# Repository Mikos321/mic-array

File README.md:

# Spidermic
 
Spidermic is an low cost circular microphone array. For use in audio measurement applications such as [ambisonics](https://github.com/AppliedAcousticsChalmers/ambisonics-for-insta360-pro).
## Features
* Low cost spherical microphone array with up to 15 omnidirection microphones.
* Plug and play compatible with [Minidsp MCHstreamer](https://www.minidsp.com/products/usb-audio-interface/mchstreamer-lite).
* 15 PDM Infineon M73D122V01 Microphones.
* No programming required!
## Repository Organization
* [kicad/](kicad/) - KiCad schematic, layout and fabrication files for both the main PCB and microhpones
* [mounts/](mounts/) - STL Files for the ring mount.
## Documentation
The main board has 15 flatflex connectors, with a 24 degree angle between them, which allows for the microphones to be mounted equidistant to each other on the hemisphere of an wooden sphere with a radius of 60mm.
### Minidsp MCH-Streamer
The main board of the mic array is mounted on top of a MiniDSP MCH-Streamer connected to J2. 
Since the Infineon microphones work with 1.8v logic and the MCH-steamer only outputs 3.3v, I used Ti-SN74LVC8T245
level shifting from 3.3V to 1.8V of the data and clock signals to and from the MCH-streamer.
### Hand solder
While it should be possible to hand solder the current version of the main board, it might be tricky since components are somewhat tightly placed around the pinheader. This should get fixed in future versions.
I cannot recommend handsoldering the microphone boards since the microphones are very particular with paste application and temperature.
JLCpcba PCBA worked with well for the microphones.
### Mounting hardware
The ring mount should be printed in PETG,fit around the sphere and the microphones are also friction fit in the "claws". 
Squeezing the ring to spread the claws makes it easier to mount the microphones as the tolerances are tight.

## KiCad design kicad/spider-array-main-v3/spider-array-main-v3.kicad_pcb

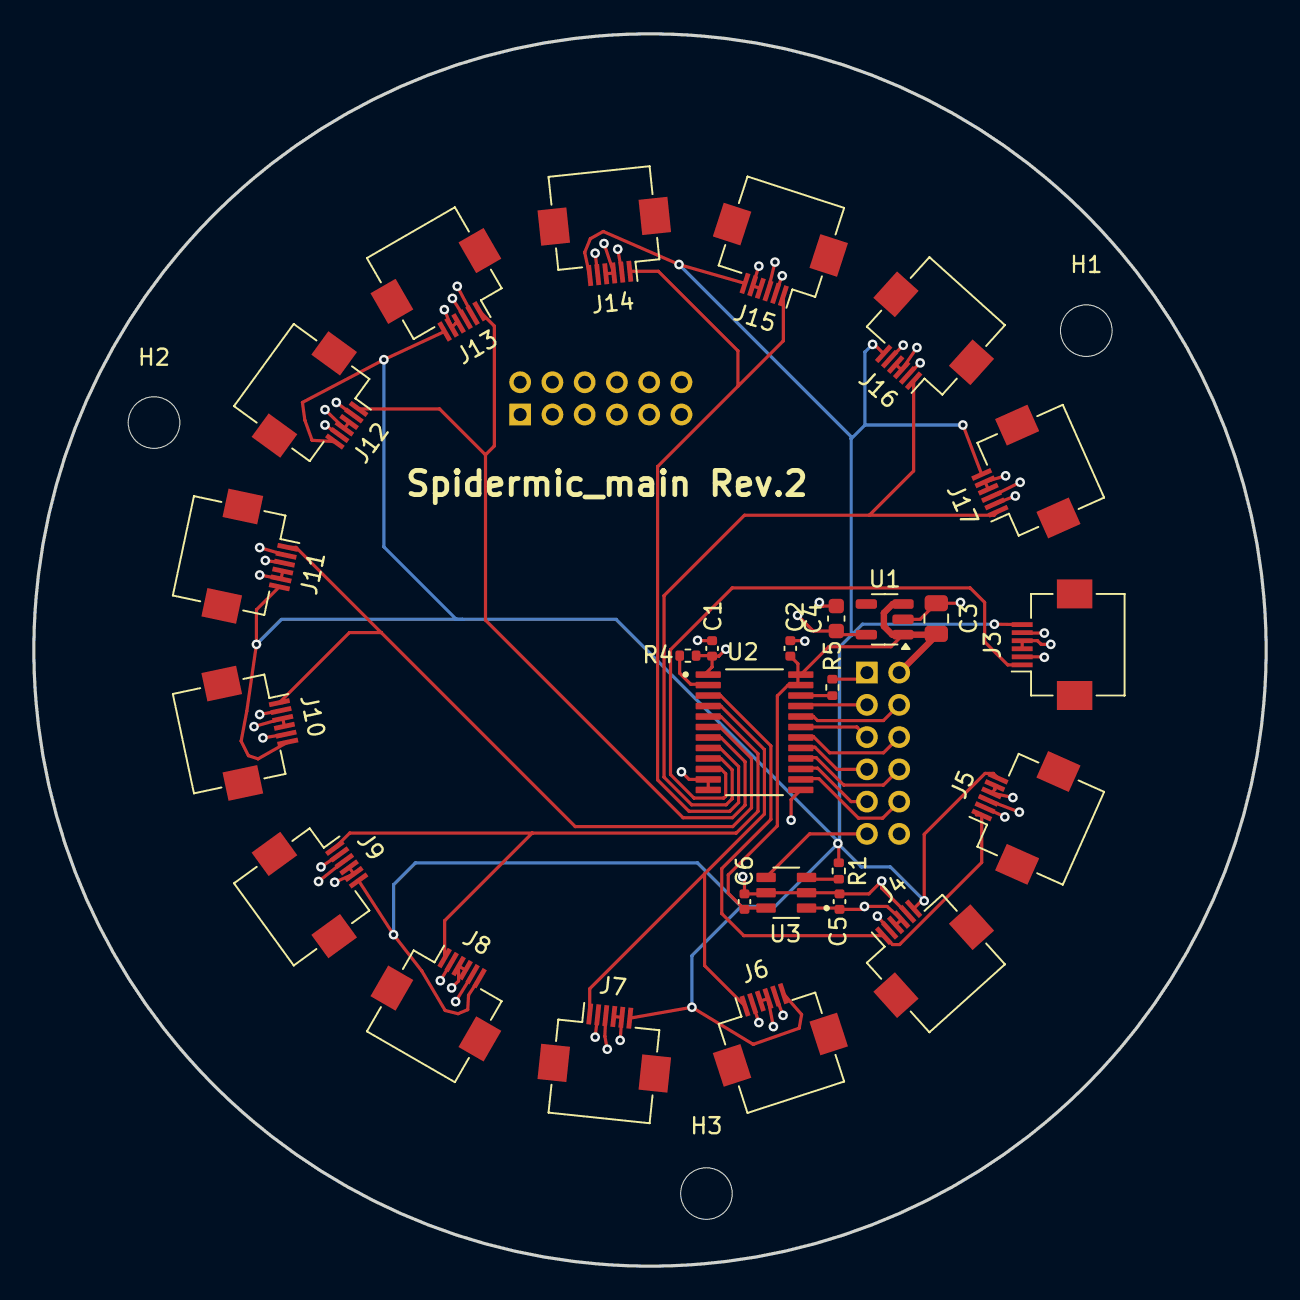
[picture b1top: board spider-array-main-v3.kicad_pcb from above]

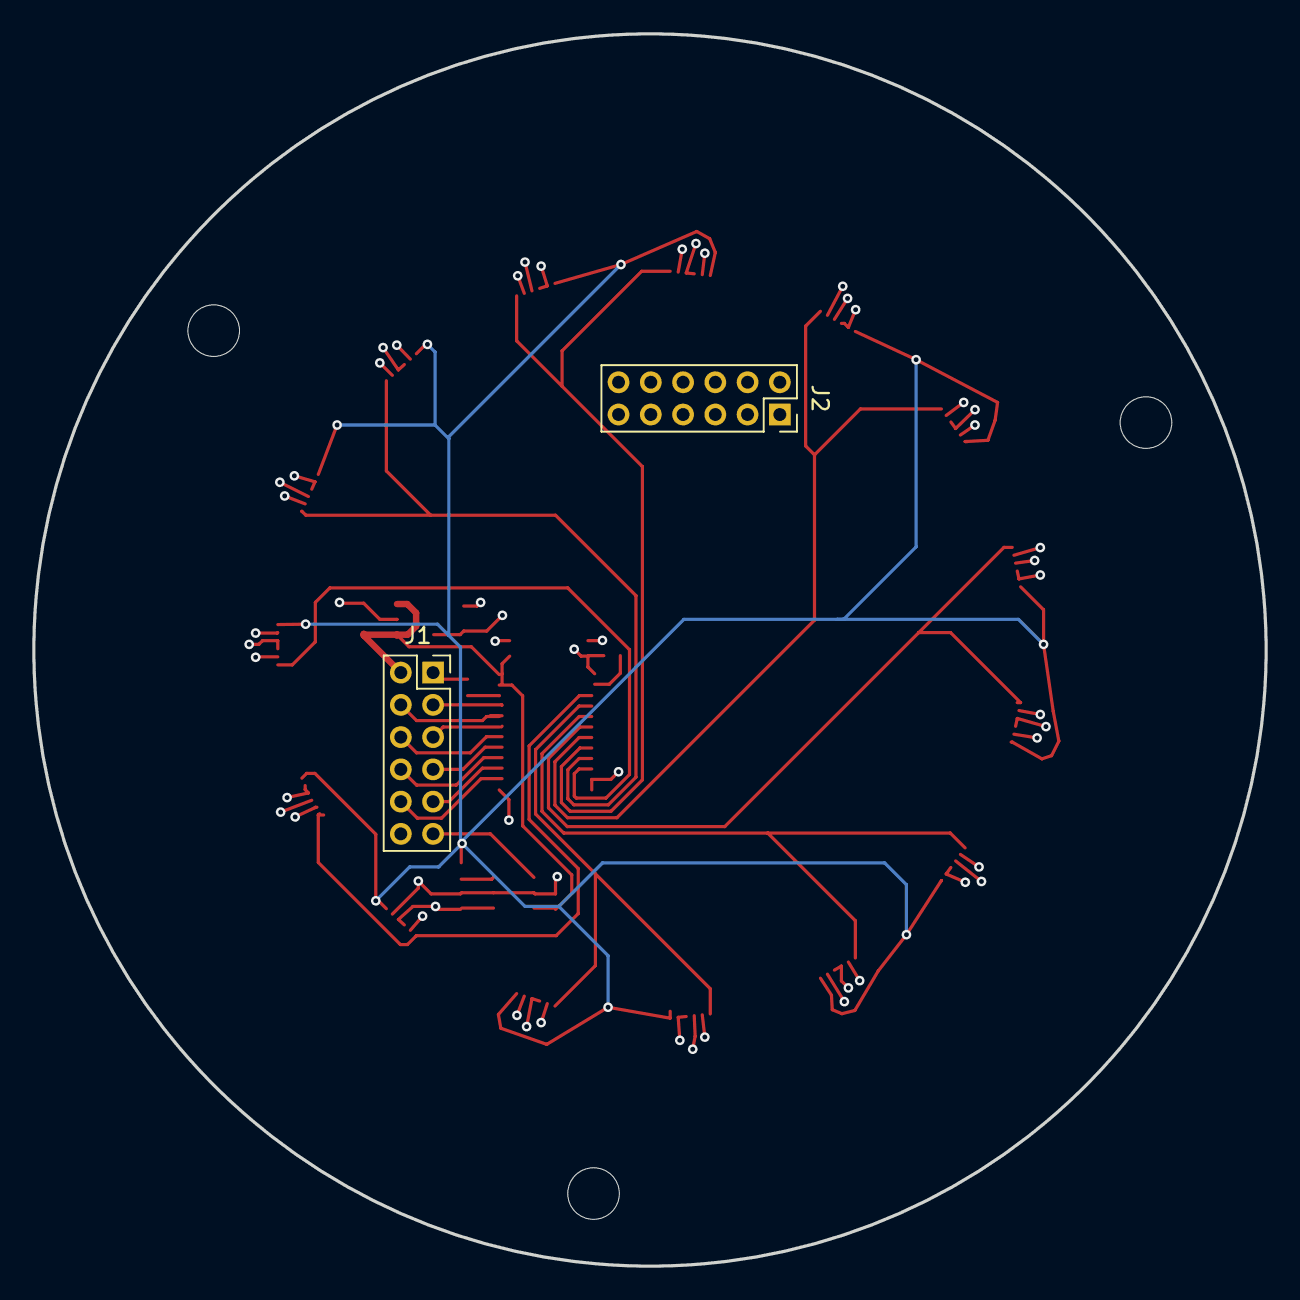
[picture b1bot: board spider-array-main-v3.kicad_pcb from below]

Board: 4 copper layers, 76.4 x 76.4 mm, 32 parts (2 on the bottom side), 24 nets.

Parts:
C1, C2, C5, C6: 1µF; C_0402_1005Metric
C3: 22µF; C_0805_2012Metric
C4: 4.7µF; C_0603_1608Metric
H1, H2, H3: MountingHole; MountingHole_3.2mm_M3
J1, J2: MCH-J3; PinSocket_2x06_P2.00mm_Vertical
J3, J4, J5, J6, J7, J8, J9, J10, J11, J12, J13, J14, J15, J16, J17: Conn_01x06_Socket; Hirose_FH12-6S-0.5SH_1x06-1MP_P0.50mm_Horizontal
R1: 220; R_0402_1005Metric
R4, R5: 2K; R_0402_1005Metric
U1: LP5907MFX-1.8; SOT-23-5
U2: SN74LVC8T245PW; SOP65P640X120-24N
U3: SN74AVCH1T45DBVR; SOT95P280X145-6N

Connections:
GND: C1.2, C2.2, C3.2, C4.2, C5.2, C6.2, J1.1, J3.2, J3.5, J4.2, J4.5, J5.2, J5.4, J5.5, J6.2, J6.5, J7.2, J7.4, J7.5, J8.2, J8.5, J9.2, J9.4, J9.5, J10.2, J10.5, J11.2, J11.4, J11.5, J12.2, J12.5, J13.2, J13.4, J13.5, J14.2, J14.5, J15.2, J15.4, J15.5, J16.2, J16.5, J17.2, J17.4, J17.5, R5.1, U1.2 (GND), U2.11 (GND), U2.12 (GND), U2.13 (GND), U3.2 (GND), U3.5 (DIR)
unnamed: R4.2, U2.2 (DIR)
unnamed: R5.2, U2.22 (~OE)
unnamed: R1.2, U3.3 (A)
PDM_CLK_0IN: J1.11, U3.4 (B)
PDM_CLK_1V8: J3.6, J4.6, J5.6, J6.6, J7.6, J8.6, J9.6, J10.6, J11.6, J12.6, J13.6, J14.6, J15.6, J16.6, J17.6, R1.1
PDM_DATA0: J1.3, U2.21 (B1)
PDM_DATA0_1V8: J4.1, J5.1, U2.3 (A1)
PDM_DATA1: J1.4, U2.20 (B2)
PDM_DATA1_1V8: J6.1, J7.1, U2.4 (A2)
PDM_DATA2: J1.5, U2.19 (B3)
PDM_DATA2_1V8: J8.1, J9.1, U2.5 (A3)
PDM_DATA3: J1.6, U2.18 (B4)
PDM_DATA3_1V8: J10.1, J11.1, U2.6 (A4)
PDM_DATA4: J1.7, U2.17 (B5)
PDM_DATA4_1V8: J12.1, J13.1, U2.7 (A5)
PDM_DATA5: J1.8, U2.16 (B6)
PDM_DATA5_1V8: J14.1, J15.1, U2.8 (A6)
PDM_DATA6: J1.9, U2.15 (B7)
PDM_DATA6_1V8: J16.1, J17.1, U2.9 (A7)
PDM_DATA7: J1.10, U2.14 (B8)
PDM_DATA7_1V8: J3.1, U2.10 (A8)
VCCA: C1.1, C4.1, C5.1, J3.3, J3.4, J4.3, J4.4, J5.3, J6.3, J6.4, J7.3, J8.3, J8.4, J9.3, J10.3, J10.4, J11.3, J12.3, J12.4, J13.3, J14.3, J14.4, J15.3, J16.3, J16.4, J17.3, R4.1, U1.5 (OUT), U2.1 (VCCA), U3.1 (VCCA)
VCCB: C2.1, C3.1, C6.1, J1.2, U1.1 (IN), U1.3 (EN), U2.23 (VCCB), U2.24 (VCCB), U3.6 (VCCB)

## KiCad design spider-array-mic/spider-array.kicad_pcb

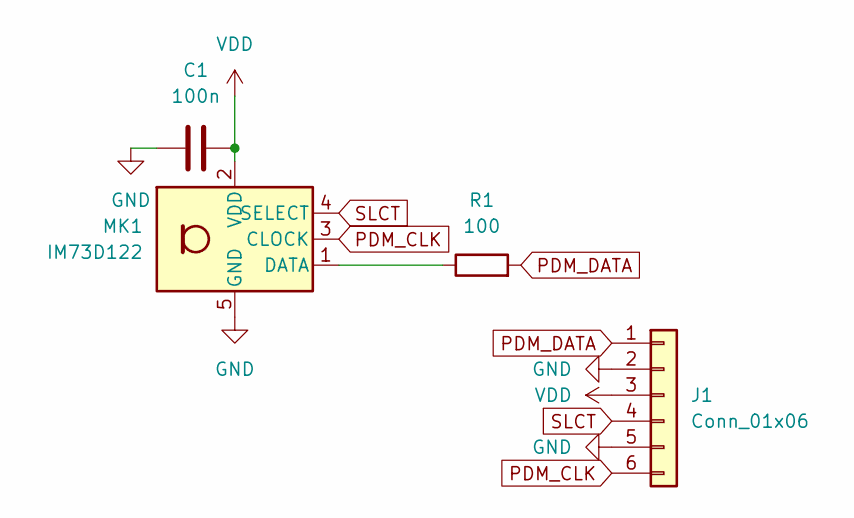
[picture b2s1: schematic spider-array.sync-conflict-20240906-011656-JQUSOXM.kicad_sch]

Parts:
C1: 100n; C_0201_0603Metric
J1: Conn_01x06; Hirose_FH12-6S-0.5SH_1x06-1MP_P0.50mm_Horizontal
MK1: IM73D122; Infineon_PG-LLGA-5-1
R1: 100; R_0201_0603Metric

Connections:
GND: C1.1, J1.2, J1.5, MK1.5 (GND)
unnamed: MK1.1 (DATA), R1.1
PDM_CLK: J1.6, MK1.3 (CLOCK)
PDM_DATA: J1.1, R1.2
SLCT: J1.4, MK1.4 (SELECT)
VDD: C1.2, J1.3, MK1.2 (VDD)

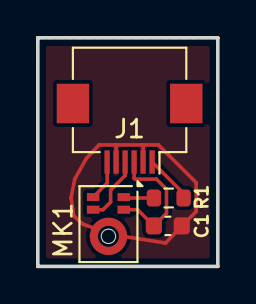
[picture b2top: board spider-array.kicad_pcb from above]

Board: 2 copper layers, 10.0 x 12.7 mm, 4 parts (0 on the bottom side), 6 nets.

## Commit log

2024-10-31 initial move to github of project files
2024-11-17 Created Readme and added pictures, mount stl files...
2024-11-17 Create LICENSE
